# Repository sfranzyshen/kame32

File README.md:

# Kame32

# License 
This robot is licensed under a [Creative Commons Attribution-ShareAlike 4.0 International License](http://creativecommons.org/licenses/by-sa/4.0/).

## this is a sfranzyshen fork ... refer to original

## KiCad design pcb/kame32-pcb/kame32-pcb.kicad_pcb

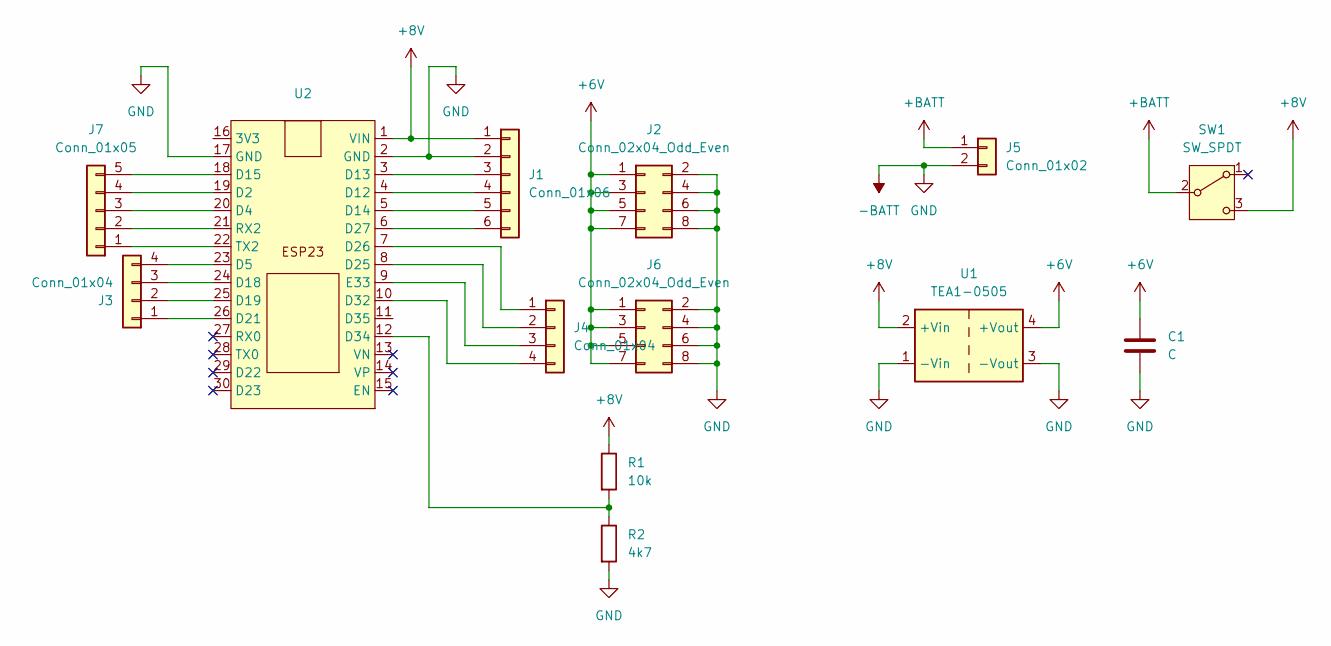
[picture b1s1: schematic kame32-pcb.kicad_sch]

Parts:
C1: C; CP_Radial_D5.0mm_P2.50mm
J1: Conn_01x06; PinHeader_1x06_P2.54mm_Vertical
J2, J6: Conn_02x04_Odd_Even; PinHeader_2x04_P2.54mm_Vertical
J3, J4: Conn_01x04; PinHeader_1x04_P2.54mm_Vertical
J5: Conn_01x02; PinHeader_1x02_P2.54mm_Vertical
J7: Conn_01x05; PinHeader_1x05_P2.54mm_Vertical
R1: 10k; R_Axial_DIN0204_L3.6mm_D1.6mm_P7.62mm_Horizontal
R2: 4k7; R_Axial_DIN0204_L3.6mm_D1.6mm_P7.62mm_Horizontal
SW1: SW_SPDT; SW_XKB_DM1-16UP-1
U1: TEA1-0505; PinHeader_2x02_P2.54mm_Vertical
U2: PinHeader_1x30_P2.54mm_Vertical

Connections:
+6V: C1.1, J2.1, J2.3, J2.5, J2.7, J6.1, J6.3, J6.5, J6.7, U1.4 (+Vout)
+8V: J1.1, R1.1, SW1.3 (C), U1.2 (+Vin), U2.1 (VIN)
+BATT: J5.1, SW1.2 (B)
-BATT: C1.2, J1.2, J2.2, J2.4, J2.6, J2.8, J5.2, J6.2, J6.4, J6.6, J6.8, R2.2, U1.1 (-Vin), U1.3 (-Vout), U2.2 (GND), U2.17 (GND)
unnamed: J1.3, U2.3 (D13)
unnamed: J1.4, U2.4 (D12)
unnamed: J1.5, U2.5 (D14)
unnamed: J1.6, U2.6 (D27)
unnamed: J3.1, U2.26 (D21)
unnamed: J3.2, U2.25 (D19)
unnamed: J3.3, U2.24 (D18)
unnamed: J3.4, U2.23 (D5)
unnamed: J4.1, U2.7 (D26)
unnamed: J4.2, U2.8 (D25)
unnamed: J4.3, U2.9 (E33)
unnamed: J4.4, U2.10 (D32)
unnamed: J7.1, U2.22 (TX2)
unnamed: J7.2, U2.21 (RX2)
unnamed: J7.3, U2.20 (D4)
unnamed: J7.4, U2.19 (D2)
unnamed: J7.5, U2.18 (D15)
unnamed: R1.2, R2.1, U2.12 (D34)

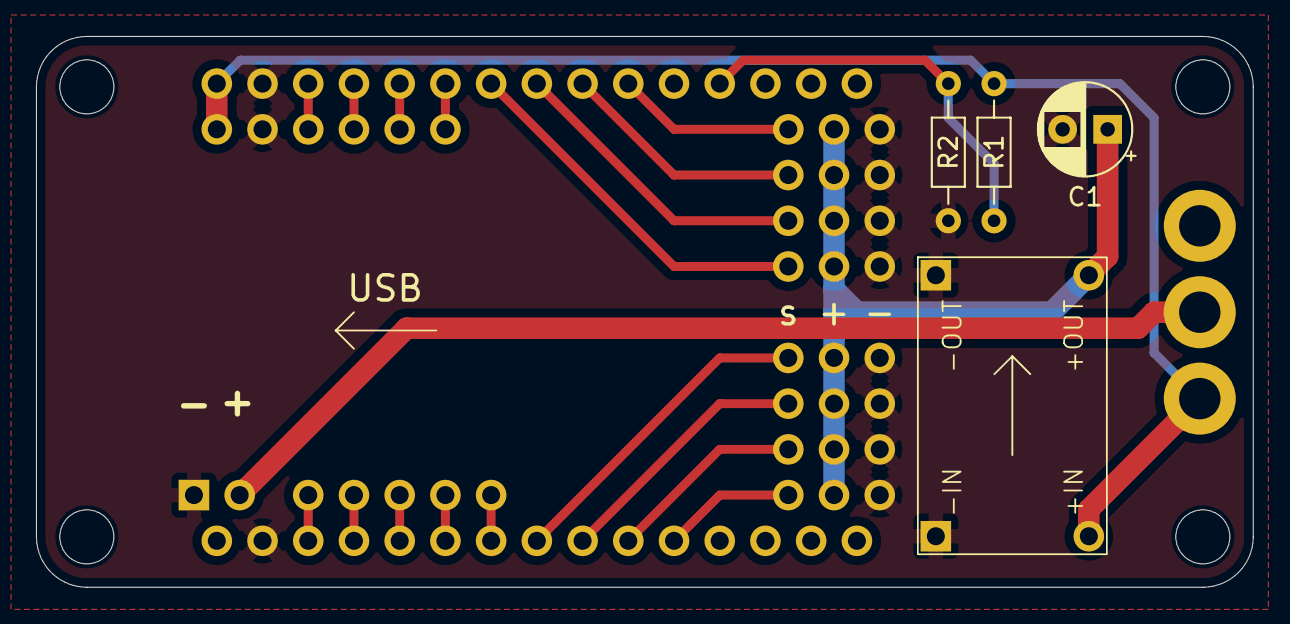
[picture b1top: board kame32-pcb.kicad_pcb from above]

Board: 2 copper layers, 67.6 x 30.6 mm, 13 parts (1 on the bottom side), 22 nets.

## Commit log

2025-04-23 pcb files
2025-04-24 3d model
2025-04-29 fix body sockets in freecad model
2025-05-08 PCB before DCDC change
2025-05-24 tested 3d model
2025-05-25 code for web teleoperation
2025-05-25 add main photo
2025-05-25 added leg-link missing part
2025-05-25 add bushing
2025-05-27 esp32 pcb with servo headers
2025-06-02 fix horn room for mg90s parts
2025-06-04 working in calibration interface
2025-06-04 improved calibration ui (dark theme matching web)
2025-06-04 bigger tolerances for mg90s parts
2025-06-07 interface to calibrate servos
2025-06-12 apply calibration values
2025-06-16 update config
2025-06-17 migrate servo control to native functions
2025-06-17 testing a web joystick
2025-06-22 WIP reconfiguring gait with joystick
2025-06-23 turn function with joystick
2025-06-23 refactor
2025-07-04 Gamepad with joystick and buttons
2025-07-06 Update 3D sources
2025-07-18 updated bushing stl

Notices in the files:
pcb/kame32-pcb/kame32-pcb.kicad_pcb:
JavierIH.com CC BY-SA
